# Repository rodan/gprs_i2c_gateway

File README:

this is a re-run of a previous project [1], 
  but instead of the Atmel AVR 328p a Texas Instruments MSP430F5510 is used

  it is still under development, but the firmware will be able to

   - talk to a number of i2c sensors
   - buffer data into a fram memory chip
   - send data via gprs to an online server
   - use a minimal amount of energy

  there are 3 components in this repository:
  firmware  - contains the C code for the microcontroller
  hardware  - open source hardware for the main board
  server    - server-side implementation of the comm protocol

  * library dependencies for the included avr software:
  none - all is included in the repo

  * compiler toolchain used (gentoo):
        msp430-gcc-4.6.3_p20120406
        msp430mcu-20120716
        msp430-binutils-2.22_p20120911
        msp430-libc-20120716
        mspdebug-0.21

  * development is done using
        MSP430-5510STK [2]

  * dependencies for the server-side software:

  sqlite      http://www.sqlite.org/
  gnuplot     http://www.gnuplot.info/

  * sensors used:

  SHT15 Humidity and Temperature Sensor
  Honeywell HSCMRNN030PA2A3 pressure sensor - mouser part: 785-HSCMRNN030PA2A3

  Author:          Petre Rodan <petre.rodan@simplex.ro>
  Available from:  https://github.com/rodan/gprs_i2c_gateway
  License:         GNU GPLv3

[1]  https://github.com/rodan/solar-sensor
[2]  https://www.olimex.com/Products/MSP430/Starter/MSP430-5510STK/

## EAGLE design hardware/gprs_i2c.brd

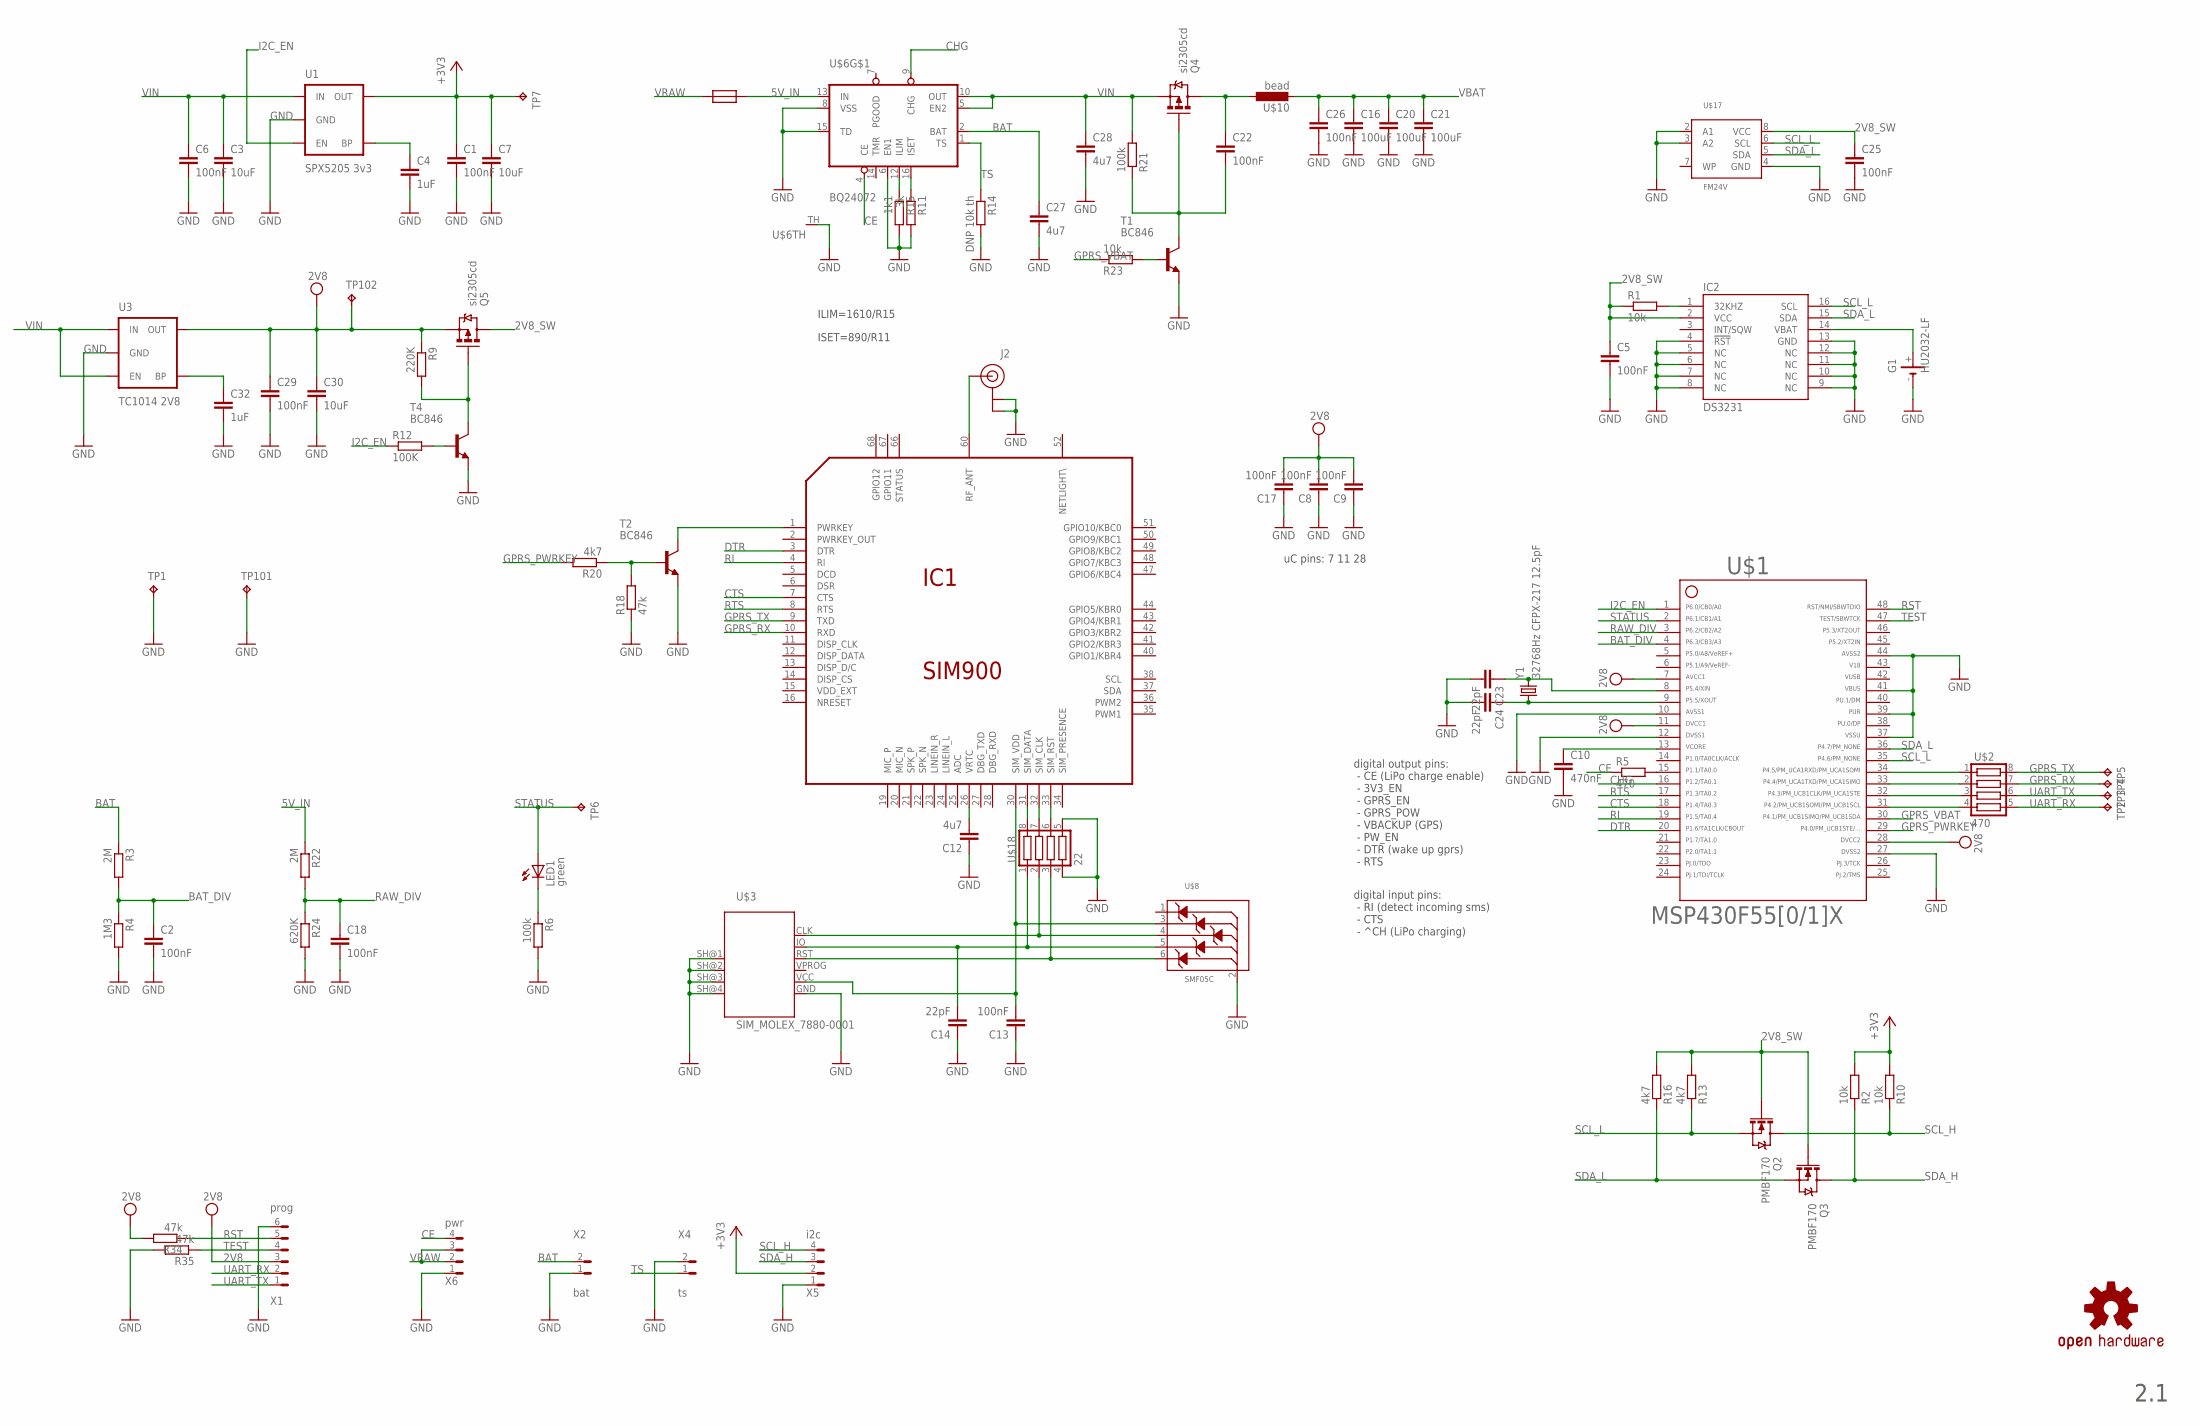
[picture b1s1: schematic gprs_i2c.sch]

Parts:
C1, C2, C5, C6, C8, C9, C13, C17, C18, C22, C25, C26, C29: 100nF; C0805
C3: 10uF; C0805
C4, C32: 1uF; C0805
C7, C30: 10uF; C1206
C10: 470nF; C0805
C12: 4u7; C0805
C14, C23, C24: 22pF; C0805
C16, C20, C21: 100uF; C1206
C27, C28: 4u7; C1206
G1: HU2032-LF
IC1: SIM900
IC2: DS3231; SO-16
J2: U.FL
LED1: green; CHIPLED_0805
Q2, Q3: PMBF170; SOT23-3
Q4, Q5: si2305cd; SOT23-3_POWER@1
R1, R2, R10, R23: 10k; R0805W
R3, R22: 2M; R0805W
R4: 1M3; R0805W
R5: 470; R0805W
R6, R21: 100k; R0805W
R9: 220K; R0805W
R11: 3k; R0805W
R12: 100K; R0805W
R13, R16, R20: 4k7; R0805W
R14: DNP 10k th; R0805W
R15: 1k1; R0805W
R18, R34, R35: 47k; R0805W
R24: 620K; R0805W
T1, T2, T4: BC846; SOT23
TP1, TP2, TP3, TP4, TP5, TP6, TP7, TP101, TP102: TPTP12R; TP12R
U1: SPX5205 3v3; SOT23-5
U3: TC1014 2V8; SOT23-5
U$1: MSP430F5510; PT48
U$2: 470; YC164
U$3: SIM_MOLEX_7880-0001; MOLEX_7880-0001
U$5: RESETTABLE_0805; 0805W
U$6: BQ24072; S-PVQFN-N16
U$7: OSHW-LOGOM; OSHW-LOGO-M
U$8: SMF05C; SC-88
U$10: bead; L0805W
U$17: FM24V; SO-08
U$18: 22; YC164
X1: prog; 0530470610
X2: bat; 0530480210
X4: ts; 0530480210
X5: i2c; 0530480401
X6: pwr; 0530480401
Y1: 32768Hz CFPX-217 12.5pF; CRYSTAL-SMD-3.2X1.5

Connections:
2V8: C8.2, C9.2, C17.2, C29.1, C30.1, Q5.2 (S), R9.1, R34.2, TP102.TP, U3.5 (OUT), U$1.7, U$1.11, U$1.28, X1.3
2V8_SW: C5.1, C25.1, IC2.2 (VCC), Q2.1 (G), Q3.1 (G), Q5.3 (D), R1.1, R13.2, R16.2, U$17.8 (VCC)
5V_IN: R22.1, U$5.2, U$6.13 (IN)
42: U$1.42
43: U$1.43
46: U$1.46
+3V3: C1.1, C7.1, R2.2, R10.2, TP7.TP, U1.5 (OUT), X5.2 (3)
BAT: C27.1, R3.1, U$6.2 (BAT), X2.2 (1)
BAT_DIV: C2.1, R3.2, R4.1, U$1.4
CE: R5.1, U$6.4 (CE), X6.4 (1)
CHG: U$1.16, U$6.9 (CHG)
CTS: IC1.7 (CTS), U$1.18
DTR: IC1.3 (DTR), U$1.20
GND: C1.2, C2.2, C3.2, C4.2, C5.2, C6.2, C7.2, C8.1, C9.1, C10.2, C12.1, C13.1, C14.1, C16.2, C17.1, C18.2, C20.2, C21.2, C23.2, C24.2, C25.2, C26.2, C27.2, C28.2, C29.2, C30.2, C32.2, G1.-, IC1.17 (GND), IC1.18 (GND), IC1.29 (GND), IC1.39 (GND), IC1.45 (GND), IC1.46 (GND), IC1.53 (GND), IC1.54 (GND), IC1.58 (GND), IC1.59 (GND), IC1.61 (GND), IC1.62 (GND), IC1.63 (GND), IC1.64 (GND), IC1.65 (GND), IC2.4 (!RST), IC2.5 (NC), IC2.6 (NC), IC2.7 (NC), IC2.8 (NC), IC2.9 (NC), IC2.10 (NC), IC2.11 (NC), IC2.12 (NC), IC2.13 (GND), J2.P$1 (GND), J2.P$2 (GND), R4.2, R6.2, R11.2, R14.2, R15.2, R18.1, R24.2, R35.2, T1.2 (E), T2.2 (E), T4.2 (E), TP1.TP, TP101.TP, U1.2 (GND), U3.2 (GND), U$1.10, U$1.12, U$1.27, U$1.37, U$1.39, U$1.41, U$1.44, U$3.GND, U$3.SH@1 (SH), U$3.SH@2 (SH), U$3.SH@3 (SH), U$3.SH@4 (SH), U$6.6 (EN1), U$6.8 (VSS), U$6.15 (TD), U$6.TH, U$8.2 (ANODE), U$17.2 (A1), U$17.3 (A2), U$17.4 (GND), U$18.4, U$18.5, X1.6, X2.1 (2), X4.2 (1), X5.1 (4), X6.1 (4)
GPRS_PWRKEY: R20.2, U$1.29
GPRS_RX: IC1.10 (RXD), TP4.TP, U$2.7
GPRS_TX: IC1.9 (TXD), TP5.TP, U$2.8
GPRS_VBAT: R23.1, U$1.30
I2C_EN: R12.1, U1.3 (EN), U$1.1
unnamed: U$1.32, U$2.3
unnamed: C4.1, U1.4 (BP)
unnamed: U$1.31, U$2.4
unnamed: U$1.33, U$2.2
unnamed: G1.+, IC2.14 (VBAT)
unnamed: C10.1, U$1.13
unnamed: R23.2, T1.1 (B)
unnamed: LED1.C, R6.1
unnamed: IC2.1 (32KHZ), R1.2
unnamed: U$1.34, U$2.1
unnamed: R5.2, U$1.15
unnamed: Q5.1 (G), R9.2, T4.3 (C)
unnamed: R12.2, T4.1 (B)
unnamed: IC1.31 (SIM_DATA), U$18.8
unnamed: IC1.32 (SIM_CLK), U$18.7
unnamed: IC1.33 (SIM_RST), U$18.6
unnamed: C24.1, U$1.9, Y1.P$1 (1)
unnamed: C23.1, U$1.8, Y1.P$2 (2)
unnamed: R11.1, U$6.16 (ISET)
unnamed: R15.1, U$6.12 (ILIM)
unnamed: R18.2, R20.1, T2.1 (B)
unnamed: IC1.60 (RF_ANT), J2.P$3 (SIGNAL)
unnamed: C22.2, Q4.1 (G), R21.1, T1.3 (C)
unnamed: C22.1, Q4.3 (D), U$10.1
unnamed: C32.1, U3.4 (BP)
PWRKEY: IC1.1 (PWRKEY), T2.3 (C)
RAW_DIV: C18.1, R22.2, R24.1, U$1.3
RI: IC1.4 (RI), U$1.19
RST: R34.1, U$1.48, X1.5
RTS: IC1.8 (RTS), U$1.17
SCL_H: Q2.3 (D), R10.1, X5.4 (1)
SCL_L: IC2.16 (SCL), Q2.2 (S), R13.1, U$1.35, U$17.6 (SCL)
SDA_H: Q3.3 (D), R2.1, X5.3 (2)
SDA_L: IC2.15 (SDA), Q3.2 (S), R16.1, U$1.36, U$17.5 (SDA)
SIMLOCK_CLK: U$3.CLK, U$8.4 (CATODE3), U$18.2
SIMLOCK_IO: C14.2, U$3.IO, U$8.5 (CATODE4), U$18.1
SIMLOCK_RST: U$3.RST, U$8.6 (CATODE5), U$18.3
SIM_VCC: C13.2, IC1.30 (SIM_VDD), U$3.VCC, U$8.3 (CATODE2)
STATUS: LED1.A, TP6.TP, U$1.2
TEST: R35.1, U$1.47, X1.4
TS: R14.1, U$6.1 (TS), X4.1 (2)
UART_RX: TP2.TP, U$2.5, X1.2
UART_TX: TP3.TP, U$2.6, X1.1
VBAT: C16.1, C20.1, C21.1, C26.1, IC1.55 (VBAT), IC1.56 (VBAT), IC1.57 (VBAT), U$10.2
VIN: C3.1, C6.1, C28.1, Q4.2 (S), R21.2, U1.1 (IN), U3.1 (IN), U3.3 (EN), U$6.5 (EN2), U$6.10 (OUT)
VRAW: U$5.1, X6.2 (3), X6.3 (2)
VRTC: C12.2, IC1.26 (VRTC)

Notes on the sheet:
2.1
uC pins: 7 11 28
digital output pins: - CE (LiPo charge enable) - 3V3_EN - GPRS_EN - GPRS_POW - VBACKUP (GPS) - PW_EN - DTR (wake up gprs) - RTS
digital input pins: - RI (detect incoming sms) - CTS - ^CH (LiPo charging)
ILIM=1610/R15
ISET=890/R11

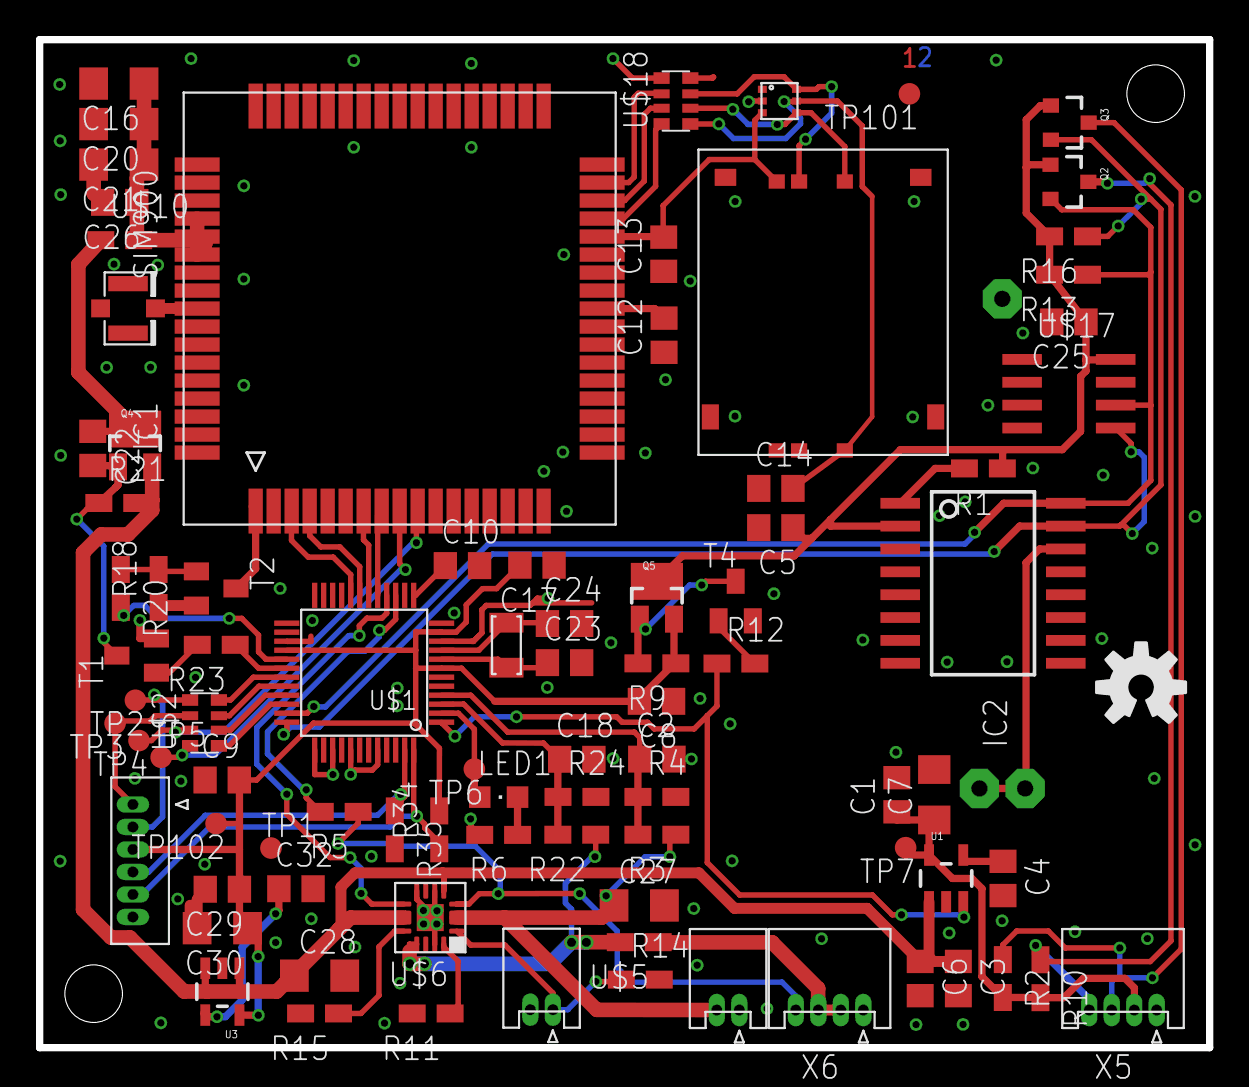
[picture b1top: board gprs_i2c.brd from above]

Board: 4 copper layers, 65.0 x 56.0 mm, 89 parts (1 on the bottom side), 63 nets.

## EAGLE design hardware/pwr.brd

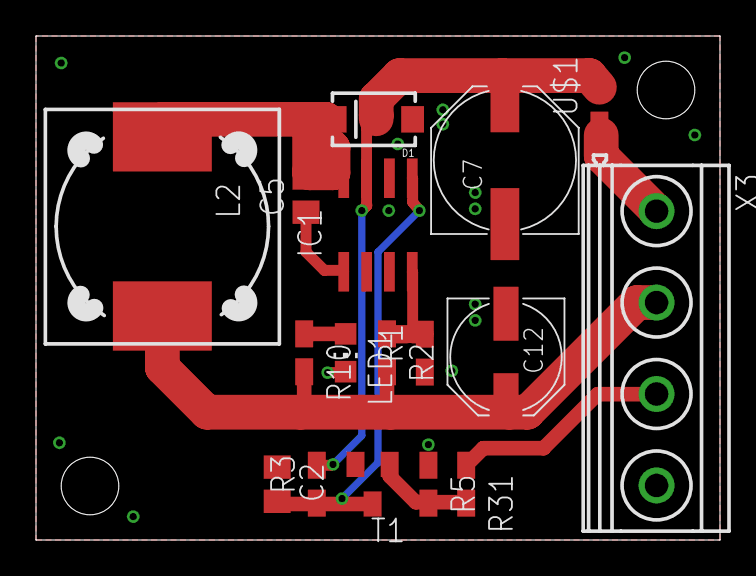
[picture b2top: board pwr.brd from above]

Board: 2 copper layers, 38.0 x 28.0 mm, 17 parts (0 on the bottom side), 11 nets.

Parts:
C2: 100nF; C0805
C5: 10nF; C0805
C7: 47uF, 63V; PANASONIC_F
C12: 100uF, 16V; PANASONIC_D
D1: 15MQ040; SMA-DIODE
IC1: SO-08
L2: 68uH 1.5A; DR125
LED1: status; CHIP-LED0805
R1: 1.5K 1%; R0805W
R2: 4k; R0805W
R3, R5: 1M; R0805W
R10: 200k; R0805W
R31: 100k; R0805W
T1: BC846; SOT23
U$1: RESETTABLE_0805; 0805W
X3: MKDSN1,5/4-5,08

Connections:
CE: R31.1, X3.3
GND: C2.1, C7.-, C12.-, D1.A, IC1.2, IC1.3, IC1.6, LED1.C, R1.1, R5.1, T1.2, X3.4
unnamed: LED1.A, R10.1
unnamed: C2.2, IC1.5, R3.1, T1.3
unnamed: R5.2, R31.2, T1.1
unnamed: IC1.4, R1.2, R2.1
unnamed: C5.2, D1.C, IC1.8, L2.1
unnamed: C5.1, IC1.1
unnamed: C7.+, IC1.7, R3.2, U$1.2
V_IN: U$1.1, X3.1
V_OUT: C12.+, L2.2, R2.2, R10.2, X3.2

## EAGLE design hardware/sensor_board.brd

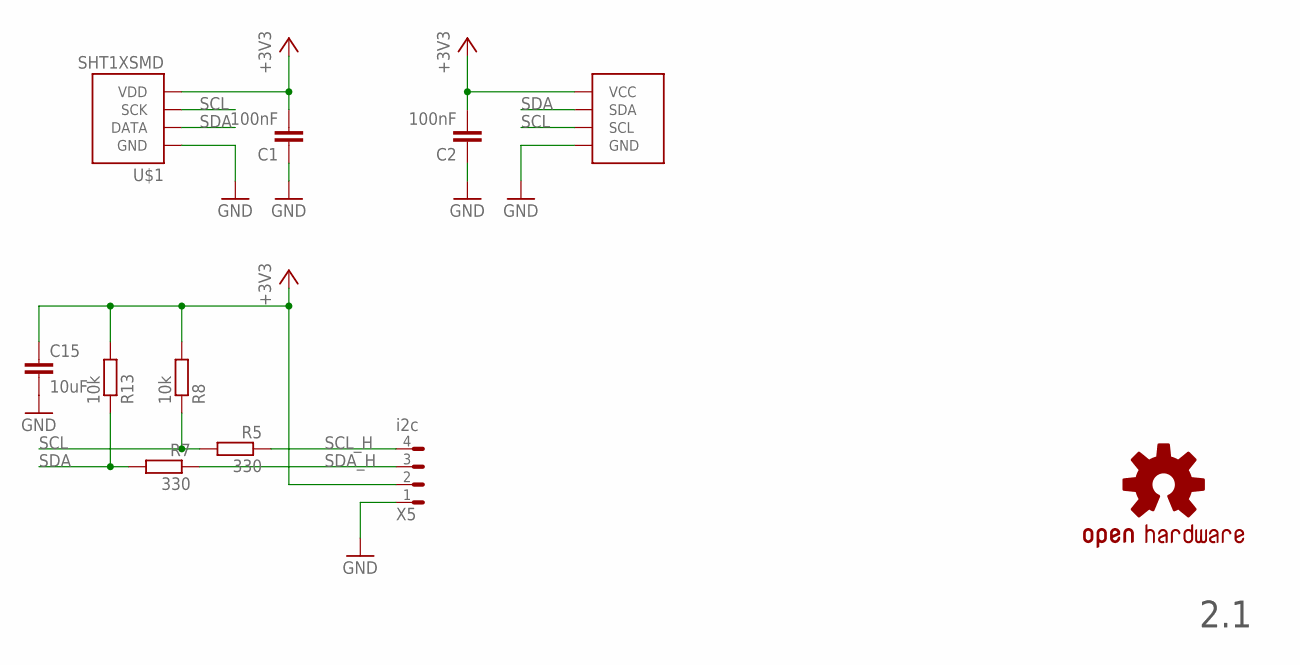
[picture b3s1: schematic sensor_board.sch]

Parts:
C1, C2: 100nF; C0805
C15: 10uF; C1206
R5, R7: 330; R0805W
R8, R13: 10k; R0805W
U$1: SHT1XSMD; SHT1X
U$2: HONEYWELL_HSC; HONEYWELL_8_SMT
U$7: OSHW-LOGOM; OSHW-LOGO-M
X5: i2c; 0530480401

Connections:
+3V3: C1.2, C2.2, C15.1, R8.2, R13.2, U$1.4 (VDD), U$2.P$2 (VCC), X5.2 (3)
GND: C1.1, C2.1, C15.2, U$1.1 (GND), U$2.P$1 (GND), X5.1 (4)
SCL: R5.2, R8.1, U$1.3 (SCK), U$2.P$4 (SCL)
SCL_H: R5.1, X5.4 (1)
SDA: R7.2, R13.1, U$1.2 (DATA), U$2.P$3 (SDA)
SDA_H: R7.1, X5.3 (2)

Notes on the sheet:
2.1

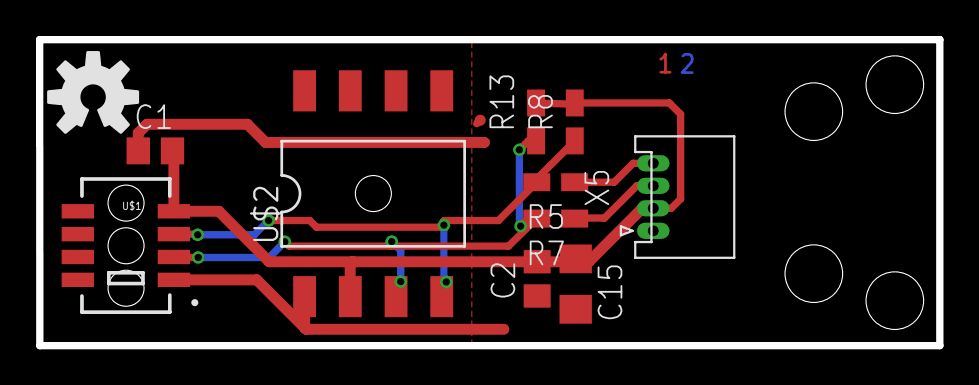
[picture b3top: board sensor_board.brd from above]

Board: 2 copper layers, 50.0 x 17.0 mm, 11 parts (0 on the bottom side), 6 nets.

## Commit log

2015-10-21 add schematic
2015-10-22 pcb routing stage1
2015-10-23 pcb reouting part2
2015-10-23 add sensor board
2015-10-28 move CE and CHG ports
2015-10-29 update port mappings
2015-10-30 pcb verified
2015-10-31 add pwr board
2015-11-01 pwr board width decrease
2015-11-01 pwr board width decrease
2015-11-01 board ready
2015-11-01 boards verified

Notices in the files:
parts and their libraries:
SparkFun-Connectors: Licensing: CC v3.0 Share-Alike You are welcome to use this library for commercial purposes.
SparkFun-DiscreteSemi: Licensing: Creative Commons ShareAlike 4.0 International - https://creativecommons.org/licenses/by-sa/4.0
